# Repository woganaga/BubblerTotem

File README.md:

# BubblerTotem

Bubble-LED-Rage-Totem: a battery-powered LED totem / bubble machine — 6
stacked rings of 27 WS2811 LEDs (162 total, an unrolled 27×6 cylinder) plus a
bubble motor, driven by an ESP32-S3 with an INMP441 I2S microphone for
sound-reactive effects.

The firmware is a customized fork of
[WLED-MM (MoonModules)](https://github.com/MoonModules/WLED-MM), chosen for
its advanced audio visualizations.

## Project layout

| Path | Status | What it is |
|---|---|---|
| [`WLED-MM/`](WLED-MM/) | **active** | Firmware: WLED-MM fork (git submodule, branch `bubbler`). Totem customizations live in its `bubbler/` folder + usermods. |
| [`BubblerAnalyzer/`](BubblerAnalyzer/) | active | Offline audio/beat-detection analysis: pulls synchronized mic WAV + DSP metadata captures from the device over WiFi and diffs the pipeline against an offline replica. |
| [`docs/`](docs/) | active (port pending) | Web Bluetooth control app (GitHub Pages). Built for the v1 firmware; will be reworked once WLED-MM gets its BLE usermod. |
| [`archive/Bubbler-pio/`](archive/Bubbler-pio/) | retired | v1 custom firmware (PlatformIO): effects engine, palettes/presets, BLE protocol, beat detection. Superseded by the WLED-MM fork; kept as reference — the beat-detection work (comb tempo picker) and BLE chunk protocol are worth porting. |
| [`archive/BubblerIno/`](archive/BubblerIno/) | retired | Original Arduino IDE sketch (v0). |

## Working with the firmware submodule

```sh
git clone --recurse-submodules https://github.com/woganaga/BubblerTotem.git
cd BubblerTotem/WLED-MM
# copy bubbler/platformio_bubbler.sample.ini -> platformio_override.ini, add WiFi creds
pio run -e bubbler_totem
```

The submodule's `origin` is the `woganaga/WLED-MM` fork; `upstream` is
MoonModules. Custom work stays on the `bubbler` branch in low-collision
surfaces (`bubbler/`, usermods, the gitignored `platformio_override.ini`) so
upstream merges stay painless.

## Hardware map

| Function | GPIO |
|---|---|
| LED chain A (rings 3,2,1 — 81 px, WS2811 GRB) | 4 |
| LED chain B (rings 4,5,6 — 81 px) | 5 |
| INMP441 mic SCK / WS / SD | 44 / 7 / 8 |
| Bubble motor (planned) | 15 |
| RS485 command receiver (planned) | 1, 2, 42 |
| Onboard status LED (active low) | 21 |

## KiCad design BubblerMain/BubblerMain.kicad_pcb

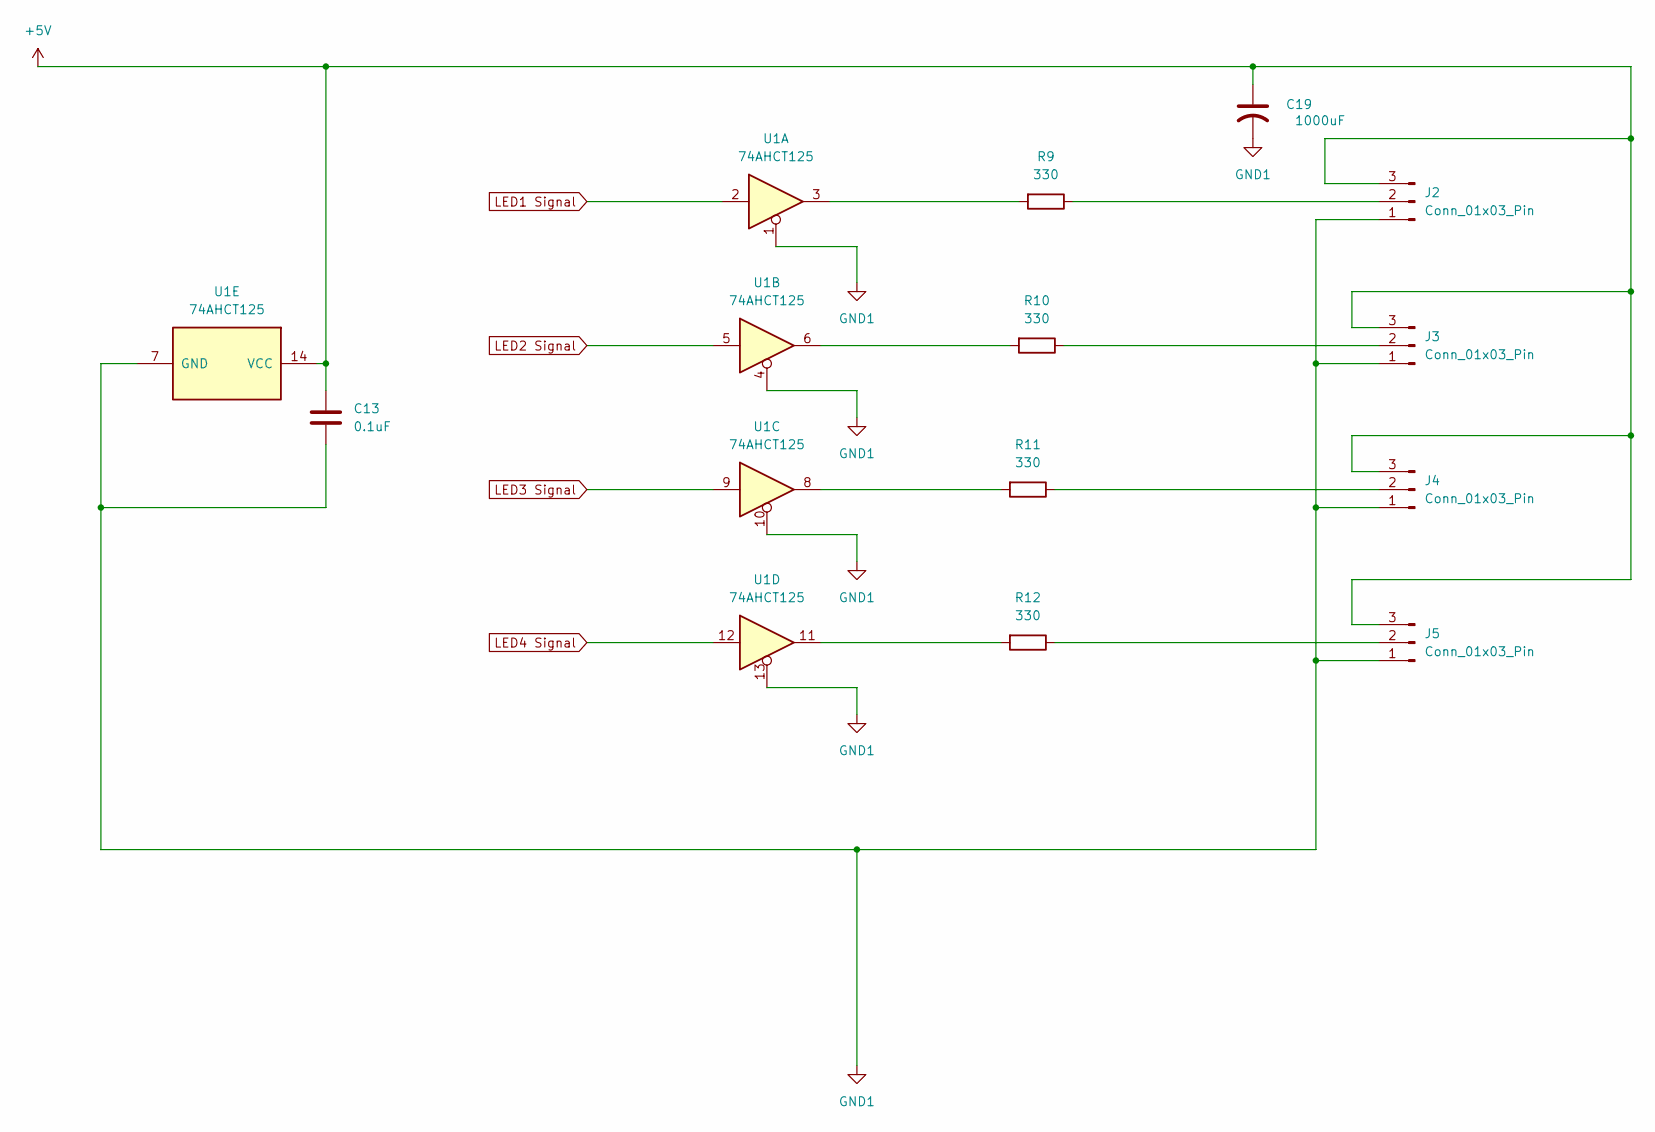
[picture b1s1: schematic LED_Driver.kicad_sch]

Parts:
C13: 0.1uF; C_1206_3216Metric_Pad1.33x1.80mm_HandSolder
C19: 1000uF; CP_Elec_10x10
J2, J3, J4, J5: Conn_01x03_Pin; JST_XH_B3B-XH-AM_1x03_P2.50mm_Vertical
R9, R10, R11, R12: 330; R_1206_3216Metric_Pad1.30x1.75mm_HandSolder
U1: 74AHCT125; SOIC-14_3.9x8.7mm_P1.27mm; LCSC C2675672

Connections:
+5V: C13.1, C19.1, J2.3, J3.3, J4.3, J5.3, U1.14 (VCC); also elsewhere on the board
GND1: C13.2, C19.2, J2.1, J3.1, J4.1, J5.1, U1.1, U1.4, U1.7 (GND), U1.10, U1.13; also elsewhere on the board
LED1 Signal: U1.2; also elsewhere on the board
LED2 Signal: U1.5; also elsewhere on the board
LED3 Signal: U1.9; also elsewhere on the board
LED4 Signal: U1.12; also elsewhere on the board
unnamed: J2.2, R9.1
unnamed: J3.2, R10.1
unnamed: J4.2, R11.1
unnamed: J5.2, R12.1
unnamed: R9.2, U1.3
unnamed: R10.2, U1.6
unnamed: R11.2, U1.8
unnamed: R12.2, U1.11

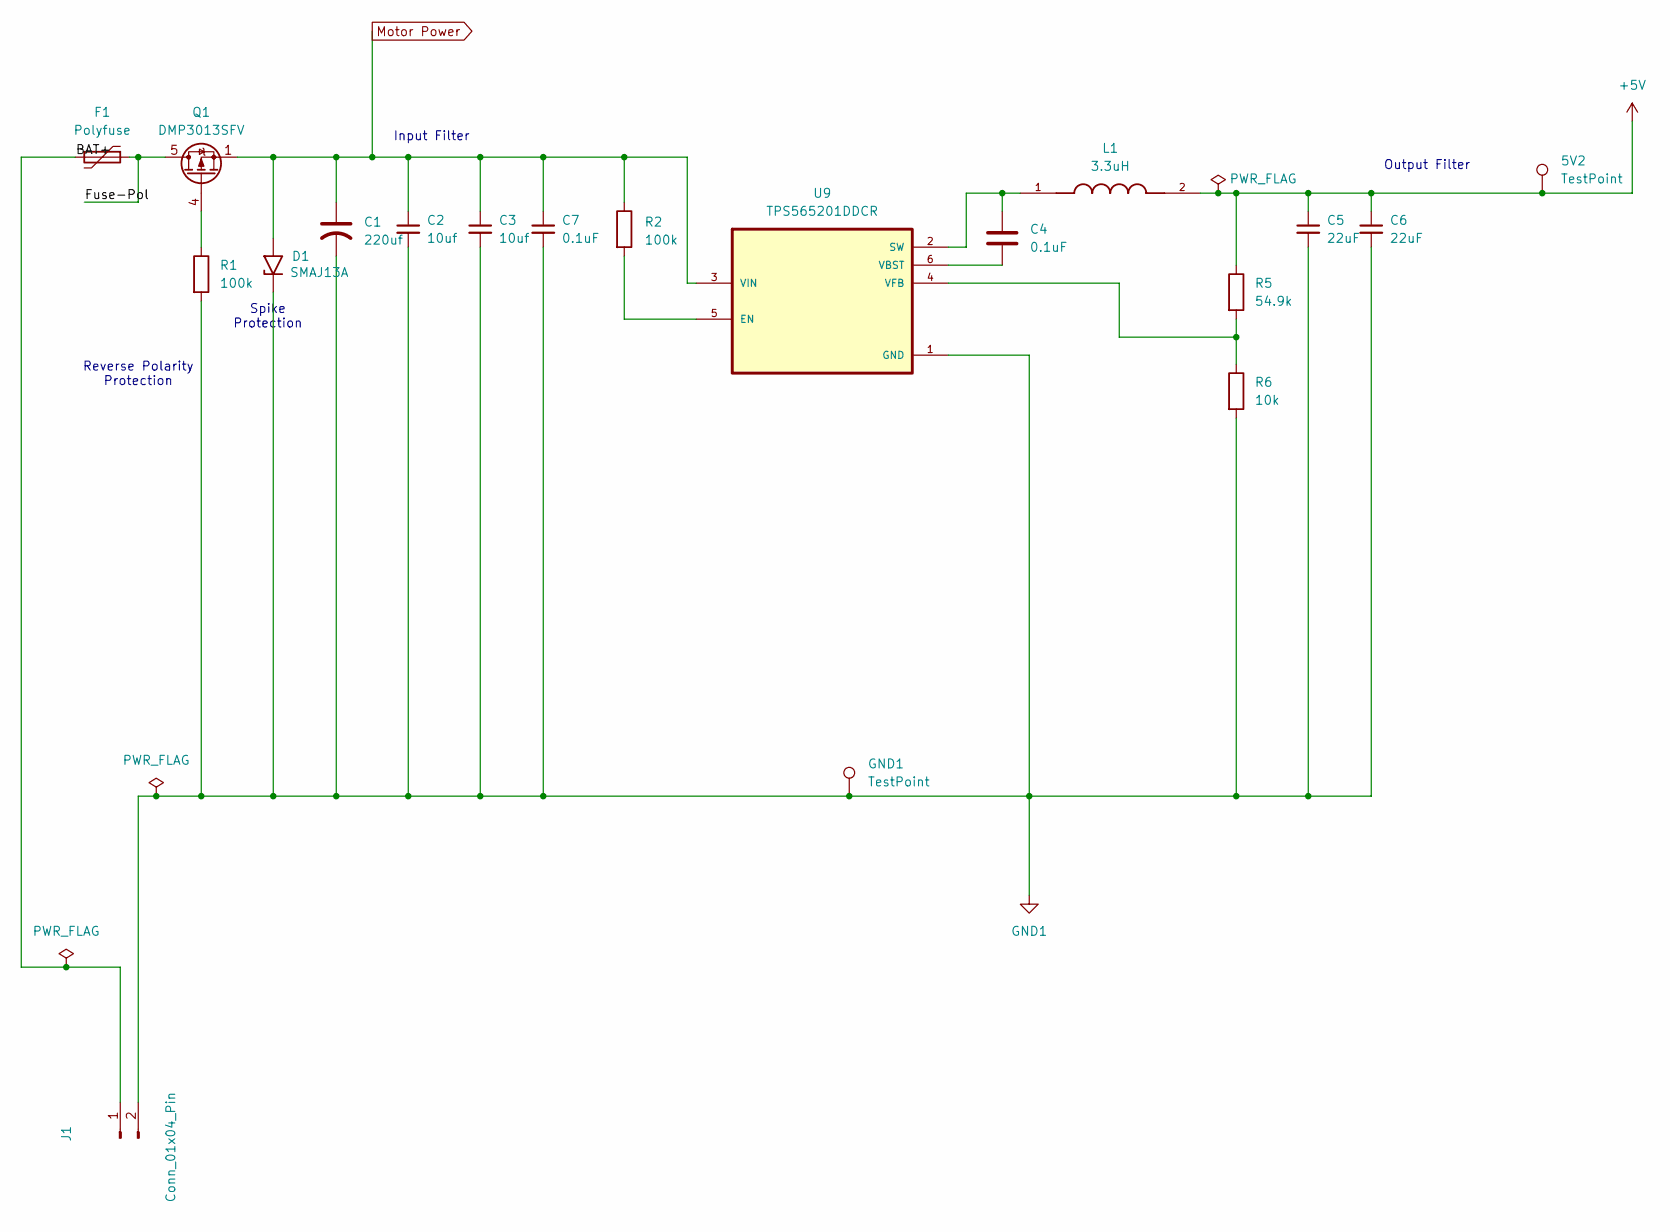
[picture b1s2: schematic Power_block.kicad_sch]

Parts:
5V2: TestPoint; TestPoint_Pad_2.0x2.0mm
C1: 220uf; CP_Elec_10x10
C2, C3: 10uf; C_1206_3216Metric_Pad1.33x1.80mm_HandSolder
C4: 0.1uF; C_1210_3225Metric_Pad1.33x2.70mm_HandSolder
C5, C6: 22uF; C_1210_3225Metric_Pad1.33x2.70mm_HandSolder
C7: 0.1uF; C_1206_3216Metric_Pad1.33x1.80mm_HandSolder
D1: SMAJ13A; D_SMA
F1: Polyfuse; Fuse_1812_4532Metric
GND1: TestPoint; TestPoint_Pad_2.0x2.0mm
J1: Conn_01x04_Pin; JST_XH_B2B-XH-AM_1x02_P2.50mm_Vertical
L1: 3.3uH; IND_SPM6530T-3R3M; PARTREV N/A; LCSC C76856
Q1: DMP3013SFV; Diodes_PowerDI3333-8; LCSC C264098
R1, R2: 100k; R_1206_3216Metric_Pad1.30x1.75mm_HandSolder
R5: 54.9k; R_1206_3216Metric_Pad1.30x1.75mm_HandSolder
R6: 10k; R_1206_3216Metric_Pad1.30x1.75mm_HandSolder
U9: TPS565201DDCR; SOT95P280X110-6N; LCSC C327676

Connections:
+5V: 5V2.1, C5.1, C6.1, L1.2, R5.1; also elsewhere on the board
/Power Block/BAT+: F1.2, J1.1
/Power Block/Fuse-Pol: F1.1, Q1.5 (D)
GND1: C1.2, C2.2, C3.2, C5.2, C6.2, C7.2, D1.1 (A1), GND1.1, J1.2, R1.2, R6.2, U9.1 (GND); also elsewhere on the board
Motor Power: C1.1, C2.1, C3.1, C7.1, D1.2 (A2), Q1.1 (S), Q1.2 (S), Q1.3 (S), R2.1, U9.3 (VIN); also elsewhere on the board
unnamed: Q1.4 (G), R1.1
unnamed: R2.2, U9.5 (EN)
unnamed: C4.1, L1.1, U9.2 (SW)
unnamed: C4.2, U9.6 (VBST)
unnamed: R5.2, R6.1, U9.4 (VFB)

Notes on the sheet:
Output Filter
Input Filter
Spike Protection
Reverse Polarity Protection

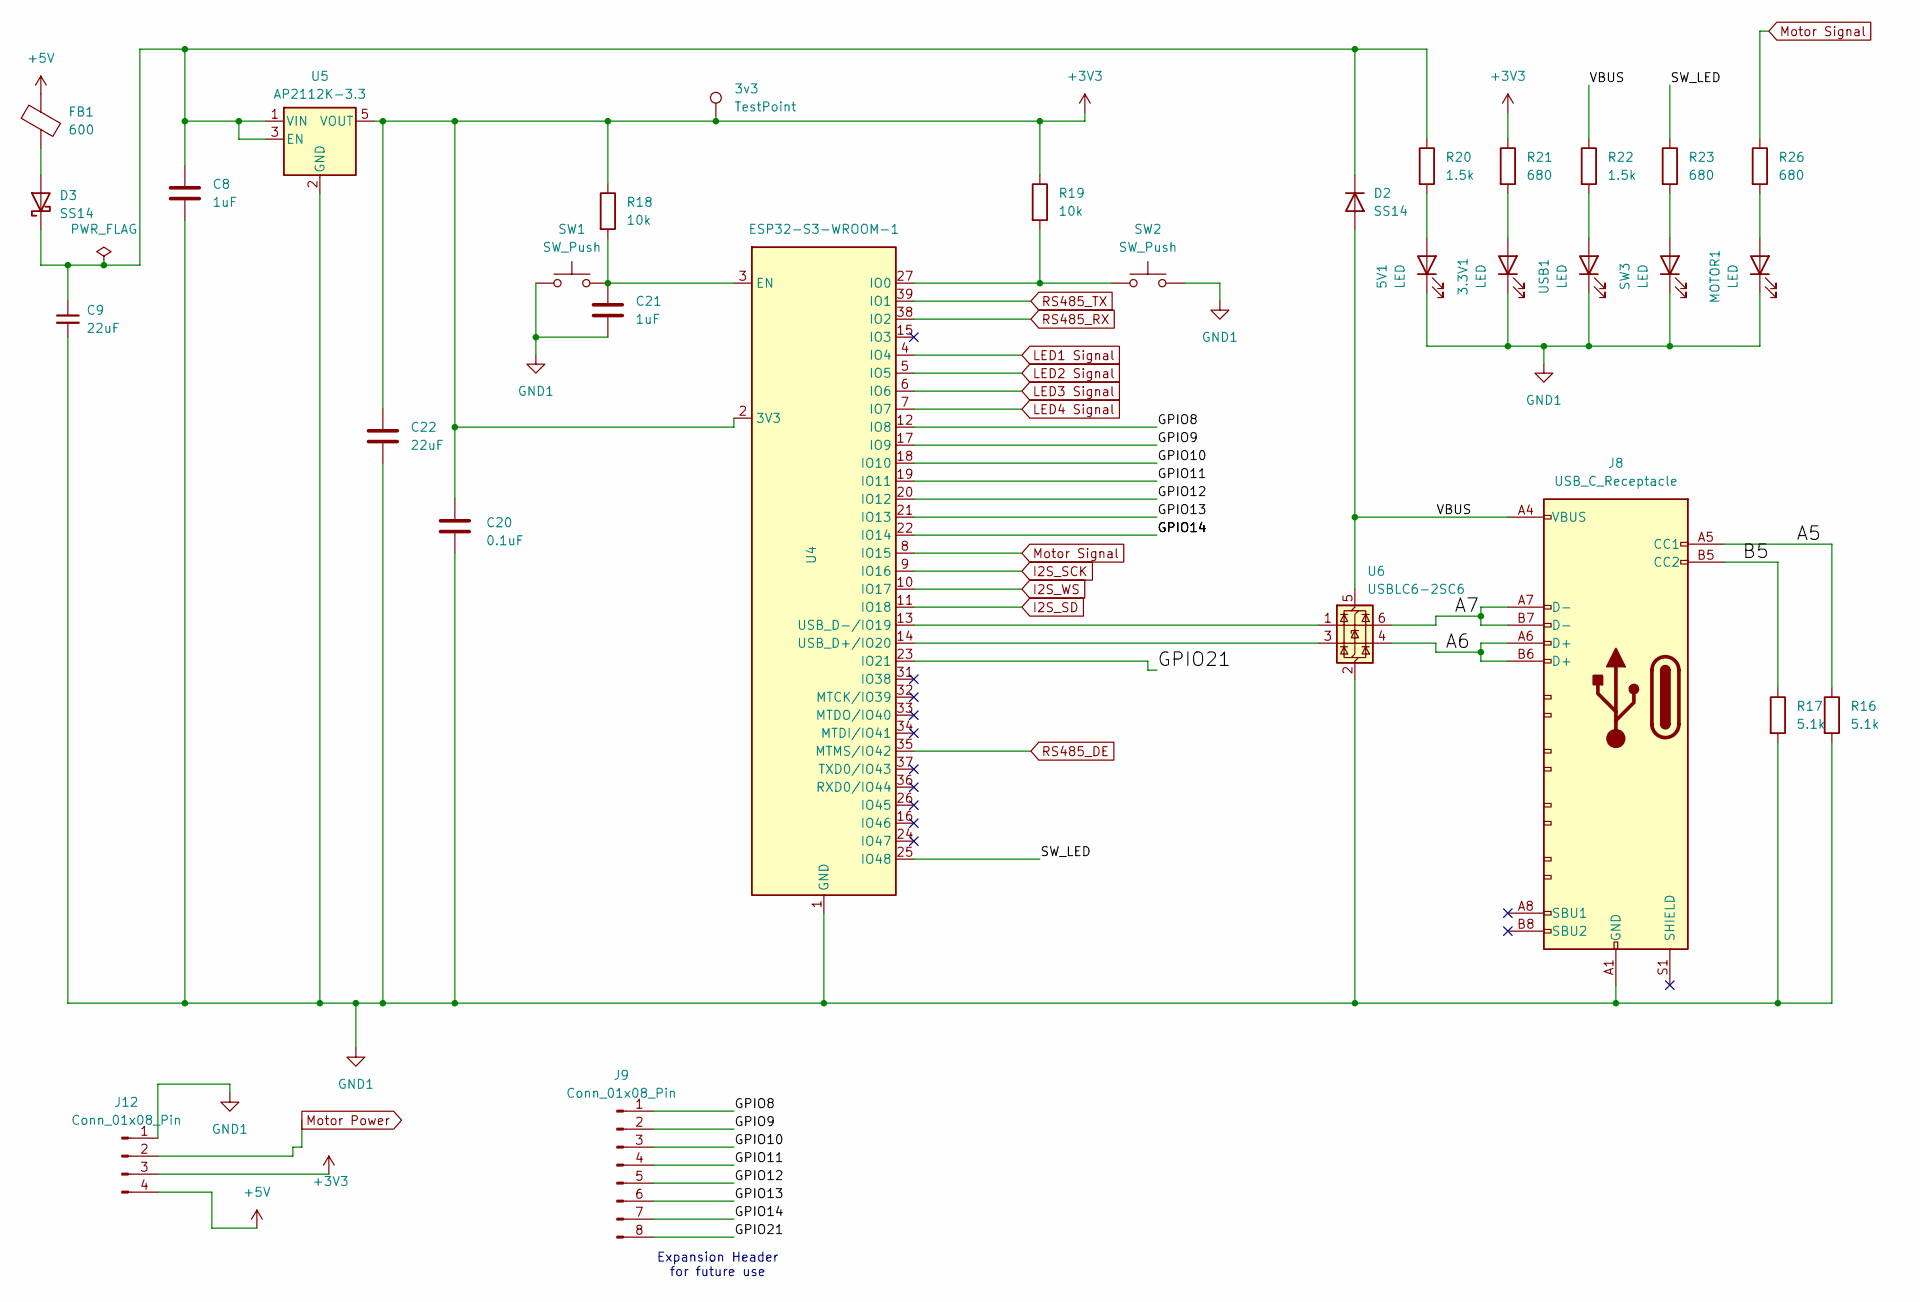
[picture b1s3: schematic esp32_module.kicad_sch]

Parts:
3.3V1, 5V1: LED; LED_1206_3216Metric_Pad1.42x1.75mm_HandSolder
3v3: TestPoint; TestPoint_Pad_2.0x2.0mm
C8, C21: 1uF; C_1206_3216Metric_Pad1.33x1.80mm_HandSolder
C9, C22: 22uF; C_1210_3225Metric_Pad1.33x2.70mm_HandSolder
C20: 0.1uF; C_1206_3216Metric_Pad1.33x1.80mm_HandSolder
D2, D3: SS14; D_SMA
FB1: 600; L_1206_3216Metric
J8: USB_C_Receptacle; USB_C_Receptacle_HCTL_HC-TYPE-C-16P-01A
J9: Conn_01x08_Pin; PinHeader_1x08_P2.54mm_Vertical
J12: Conn_01x08_Pin; PinHeader_1x04_P2.54mm_Vertical
MOTOR1: LED; LED_1206_3216Metric_Pad1.42x1.75mm_HandSolder
R16, R17: 5.1k; R_1206_3216Metric_Pad1.30x1.75mm_HandSolder
R18, R19: 10k; R_1206_3216Metric_Pad1.30x1.75mm_HandSolder
R20, R22: 1.5k; R_1206_3216Metric_Pad1.30x1.75mm_HandSolder
R21, R23, R26: 680; R_1206_3216Metric_Pad1.30x1.75mm_HandSolder
SW1, SW2: SW_Push; SW_SPST_PTS645Sx43SMTR92
SW3: LED; LED_1206_3216Metric_Pad1.42x1.75mm_HandSolder
U4: ESP32-S3-WROOM-1; ESP32-S3-WROOM-2; LCSC C2913198
U5: AP2112K-3.3; SOT-23-5; LCSC C23380830
U6: USBLC6-2SC6; SOT-23-6; LCSC C2827654
USB1: LED; LED_1206_3216Metric_Pad1.42x1.75mm_HandSolder

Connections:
+3V3: 3v3.1, C20.1, C22.1, J12.3, R18.1, R19.1, R21.1, U4.2 (3V3), U5.5 (VOUT); also elsewhere on the board
+5V: FB1.1, J12.4; also elsewhere on the board
/ESP32/A6: J8.A6 (D+), J8.B6 (D+), U6.4 (I/O2)
/ESP32/A7: J8.A7 (D-), J8.B7 (D-), U6.6 (I/O1)
/ESP32/GPIO8: J9.1, U4.12 (IO8)
/ESP32/GPIO9: J9.2, U4.17 (IO9)
/ESP32/GPIO10: J9.3, U4.18 (IO10)
/ESP32/GPIO11: J9.4, U4.19 (IO11)
/ESP32/GPIO12: J9.5, U4.20 (IO12)
/ESP32/GPIO13: J9.6, U4.21 (IO13)
/ESP32/GPIO14: J9.7, U4.22 (IO14)
/ESP32/GPIO21: J9.8, U4.23 (IO21)
/ESP32/SW_LED: R23.1, U4.25 (IO48)
/ESP32/VBUS: D2.2 (A), J8.A4 (VBUS), J8.A9 (VBUS), J8.B4 (VBUS), J8.B9 (VBUS), R22.1, U6.5 (VBUS)
GND1: 3.3V1.1 (K), 5V1.1 (K), C8.2, C9.2, C20.2, C21.2, C22.2, J8.A1 (GND), J8.A12 (GND), J8.B1 (GND), J8.B12 (GND), J12.1, MOTOR1.1 (K), R16.2, R17.2, SW1.1, SW2.2, SW3.1 (K), U4.1 (GND), U4.40 (GND), U4.41 (GND), U5.2 (GND), U6.2 (GND), USB1.1 (K); also elsewhere on the board
I2S_SCK: U4.9 (IO16); also elsewhere on the board
I2S_SD: U4.11 (IO18); also elsewhere on the board
I2S_WS: U4.10 (IO17); also elsewhere on the board
LED1 Signal: U4.4 (IO4); also elsewhere on the board
LED2 Signal: U4.5 (IO5); also elsewhere on the board
LED3 Signal: U4.6 (IO6); also elsewhere on the board
LED4 Signal: U4.7 (IO7); also elsewhere on the board
Motor Power: J12.2; also elsewhere on the board
Motor Signal: R26.1, U4.8 (IO15); also elsewhere on the board
unnamed 26: 3.3V1.2 (A), R21.2; also elsewhere on the board
unnamed 27: 5V1.2 (A), R20.2; also elsewhere on the board
unnamed: C8.1, C9.1, D2.1 (K), D3.1 (K), R20.1, U5.1 (VIN), U5.3 (EN)
unnamed: D3.2 (A), FB1.2
unnamed: MOTOR1.2 (A), R26.2
unnamed 45: R23.2, SW3.2 (A); also elsewhere on the board
unnamed: C21.1, R18.2, SW1.2, U4.3 (EN)
unnamed: R19.2, SW2.1, U4.27 (IO0)
unnamed: U4.14 (USB_D+/IO20), U6.3 (I/O2)
unnamed: U4.13 (USB_D-/IO19), U6.1 (I/O1)
unnamed 57: R22.2, USB1.2 (A); also elsewhere on the board
RS485_DE: U4.35 (MTMS/IO42); also elsewhere on the board
RS485_RX: U4.38 (IO2); also elsewhere on the board
RS485_TX: U4.39 (IO1); also elsewhere on the board

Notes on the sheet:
Expansion Header for future use

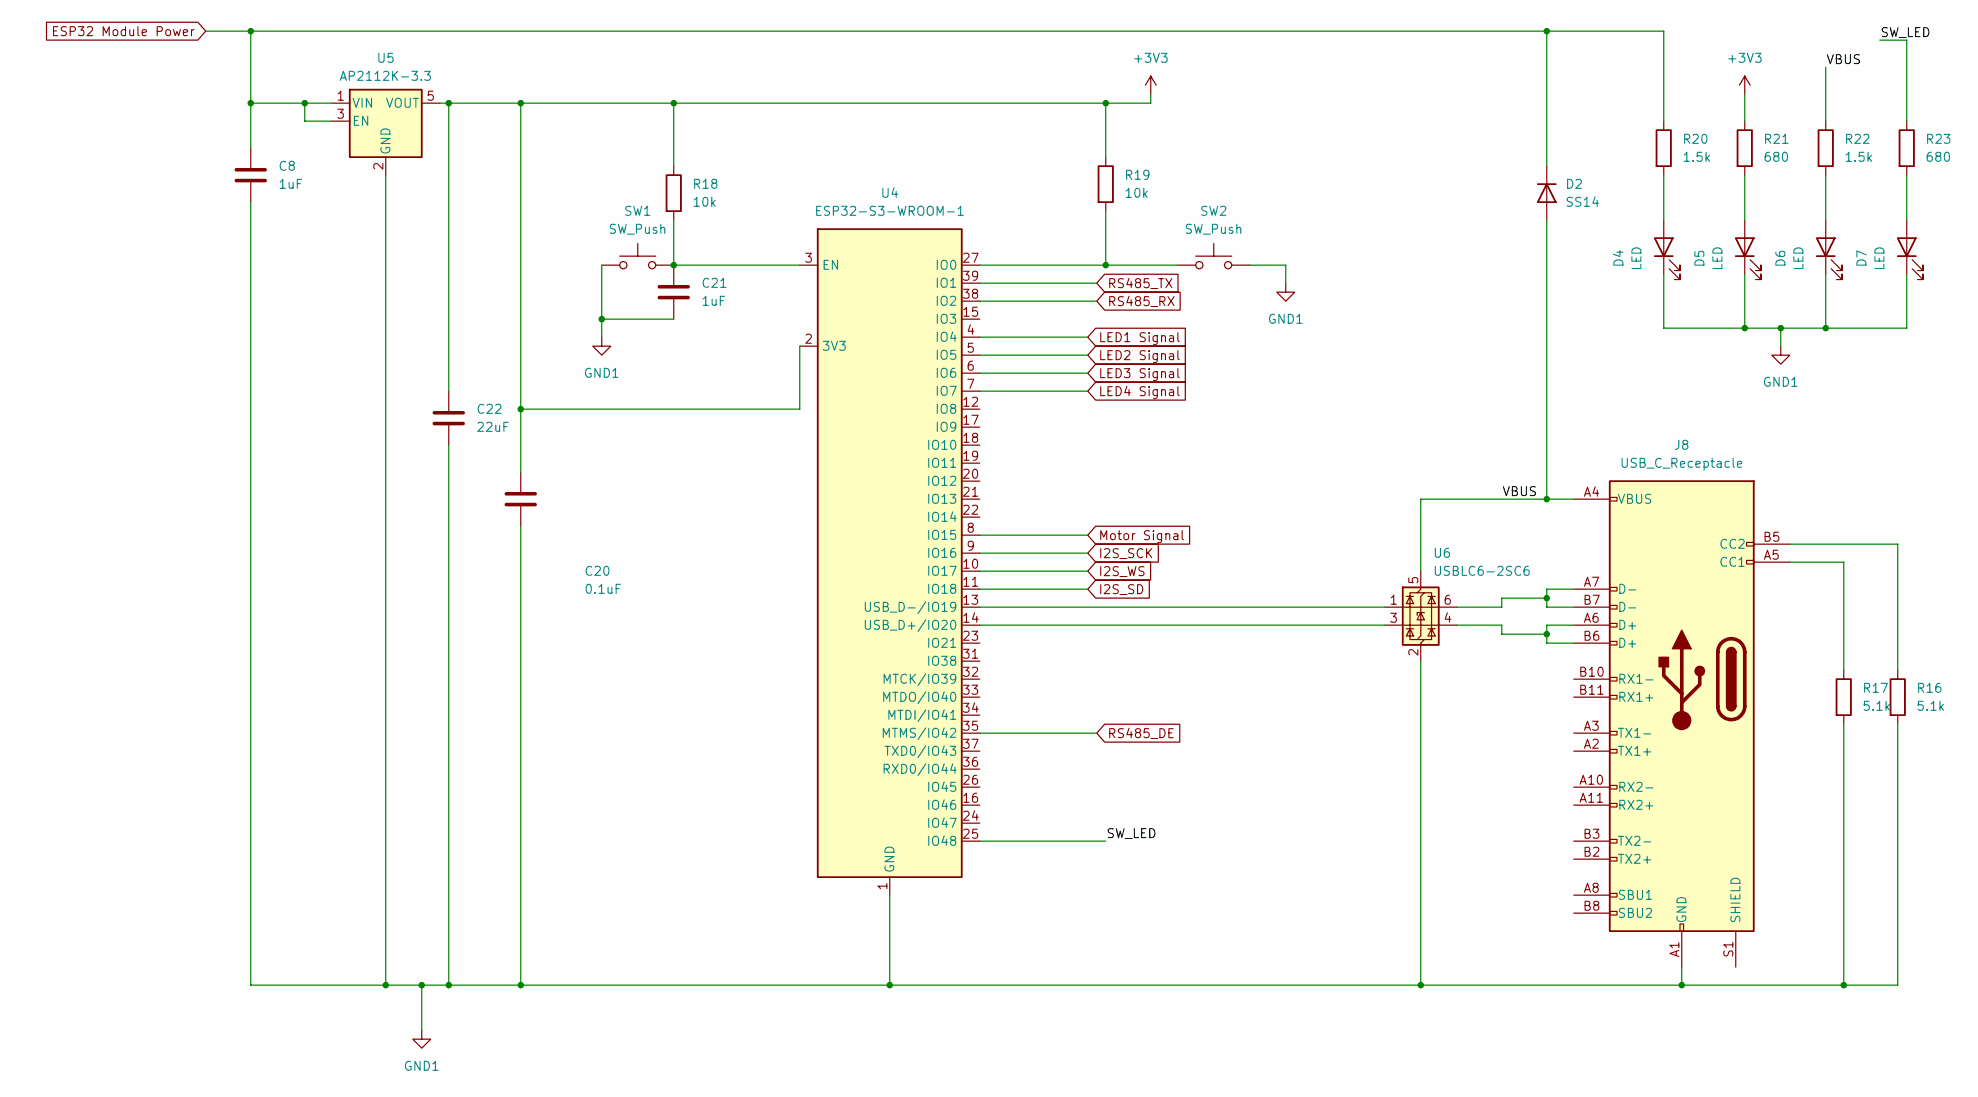
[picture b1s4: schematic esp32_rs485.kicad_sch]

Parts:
C8, C21: 1uF
C20: 0.1uF
C22: 22uF
D2: SS14
D4, D5, D6, D7: LED
J8: USB_C_Receptacle
R16, R17: 5.1k
R18, R19: 10k
R20, R22: 1.5k
R21, R23: 680
SW1, SW2: SW_Push
U4: ESP32-S3-WROOM-1; ESP32-S3-WROOM-2
U5: AP2112K-3.3; SOT-23-5
U6: USBLC6-2SC6; SOT-23-6

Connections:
+3V3: C20.1, C22.1, R18.1, R19.1, R21.1, U4.2 (3V3), U5.5 (VOUT); also elsewhere on the board
/ESP32/A6: J8.A6 (D+), J8.B6 (D+), U6.4 (I/O2)
/ESP32/A7: J8.A7 (D-), J8.B7 (D-), U6.6 (I/O1)
/ESP32/GPIO8: U4.12 (IO8); also elsewhere on the board
/ESP32/GPIO9: U4.17 (IO9); also elsewhere on the board
/ESP32/GPIO10: U4.18 (IO10); also elsewhere on the board
/ESP32/GPIO11: U4.19 (IO11); also elsewhere on the board
/ESP32/GPIO12: U4.20 (IO12); also elsewhere on the board
/ESP32/GPIO13: U4.21 (IO13); also elsewhere on the board
/ESP32/GPIO14: U4.22 (IO14); also elsewhere on the board
/ESP32/GPIO21: U4.23 (IO21); also elsewhere on the board
/ESP32/SW_LED: R23.1, U4.25 (IO48)
/ESP32/VBUS: D2.2 (A), J8.A4 (VBUS), J8.A9 (VBUS), J8.B4 (VBUS), J8.B9 (VBUS), R22.1, U6.5 (VBUS)
GND1: C8.2, C20.2, C21.2, C22.2, D4.1 (K), D5.1 (K), D6.1 (K), D7.1 (K), J8.A1 (GND), J8.A12 (GND), J8.B1 (GND), J8.B12 (GND), R16.2, R17.2, SW1.1, SW2.2, U4.1 (GND), U4.40 (GND), U4.41 (GND), U5.2 (GND), U6.2 (GND); also elsewhere on the board
I2S_SCK: U4.9 (IO16); also elsewhere on the board
I2S_SD: U4.11 (IO18); also elsewhere on the board
I2S_WS: U4.10 (IO17); also elsewhere on the board
LED1 Signal: U4.4 (IO4); also elsewhere on the board
LED2 Signal: U4.5 (IO5); also elsewhere on the board
LED3 Signal: U4.6 (IO6); also elsewhere on the board
LED4 Signal: U4.7 (IO7); also elsewhere on the board
Motor Signal: U4.8 (IO15); also elsewhere on the board
unnamed 26: D5.2 (A), R21.2; also elsewhere on the board
unnamed 27: D4.2 (A), R20.2; also elsewhere on the board
unnamed 28: C8.1, D2.1 (K), R20.1, U5.1 (VIN), U5.3 (EN); also elsewhere on the board
unnamed 45: D7.2 (A), R23.2; also elsewhere on the board
unnamed: C21.1, R18.2, SW1.2, U4.3 (EN)
unnamed: R19.2, SW2.1, U4.27 (IO0)
unnamed: U4.14 (USB_D+/IO20), U6.3 (I/O2)
unnamed: U4.13 (USB_D-/IO19), U6.1 (I/O1)
unnamed 57: D6.2 (A), R22.2; also elsewhere on the board
RS485_DE: U4.35 (MTMS/IO42); also elsewhere on the board
RS485_RX: U4.38 (IO2); also elsewhere on the board
RS485_TX: U4.39 (IO1); also elsewhere on the board

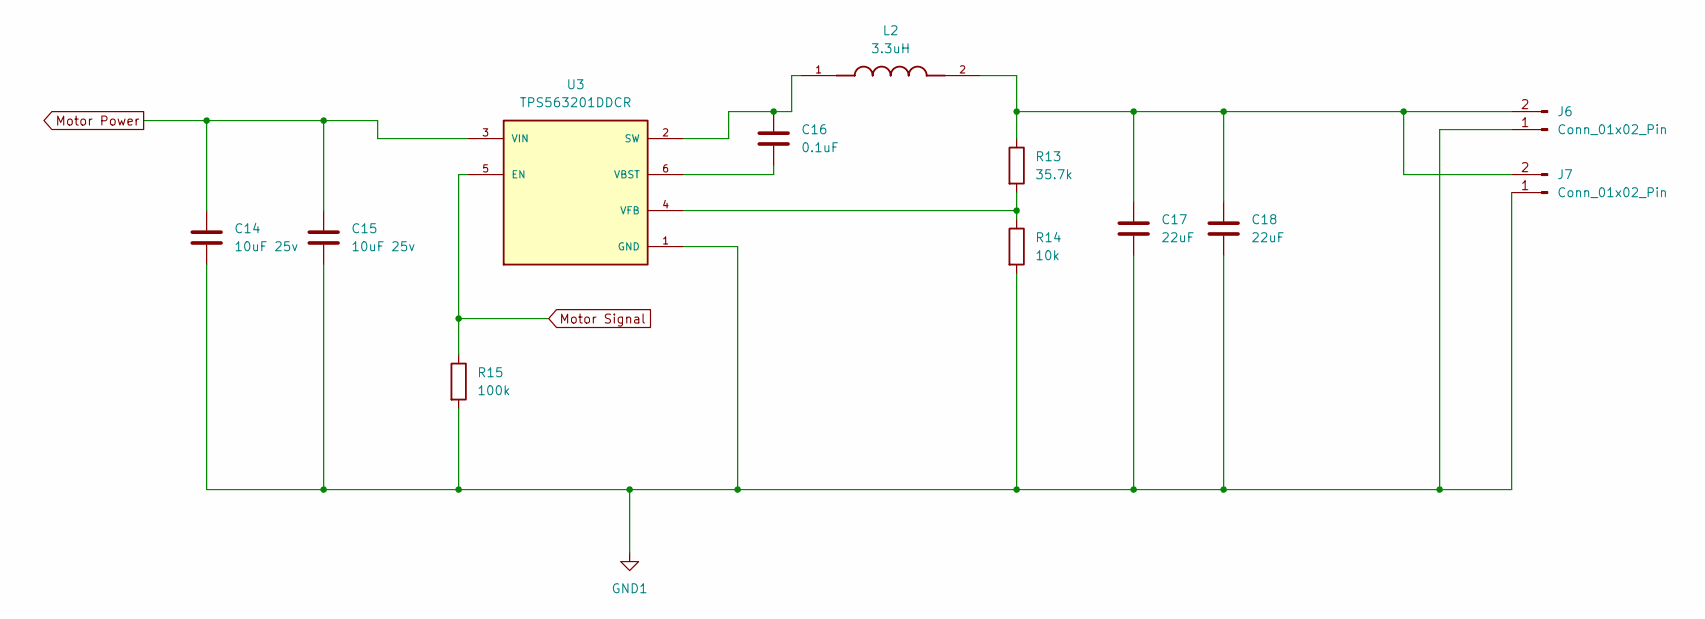
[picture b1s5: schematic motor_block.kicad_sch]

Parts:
C14, C15: 10uF 25v; C_1206_3216Metric_Pad1.33x1.80mm_HandSolder
C16: 0.1uF; C_1206_3216Metric_Pad1.33x1.80mm_HandSolder
C17, C18: 22uF; C_1210_3225Metric_Pad1.33x2.70mm_HandSolder
J6, J7: Conn_01x02_Pin; JST_XH_B2B-XH-AM_1x02_P2.50mm_Vertical
L2: 3.3uH; IND_SPM6530T-3R3M; PARTREV N/A; LCSC C76856
R13: 35.7k; R_1206_3216Metric_Pad1.30x1.75mm_HandSolder
R14: 10k; R_1206_3216Metric_Pad1.30x1.75mm_HandSolder
R15: 100k; R_1206_3216Metric_Pad1.30x1.75mm_HandSolder
U3: TPS563201DDCR; TSOT-23-6_HandSoldering; PARTREV December 2015; LCSC C116592

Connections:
GND1: C14.2, C15.2, C17.2, C18.2, J6.1, J7.1, R14.2, R15.2, U3.1 (GND); also elsewhere on the board
Motor Power: C14.1, C15.1, U3.3 (VIN); also elsewhere on the board
Motor Signal: R15.1, U3.5 (EN); also elsewhere on the board
unnamed: C17.1, C18.1, J6.2, J7.2, L2.2, R13.1
unnamed: C16.1, L2.1, U3.2 (SW)
unnamed: C16.2, U3.6 (VBST)
unnamed: R13.2, R14.1, U3.4 (VFB)

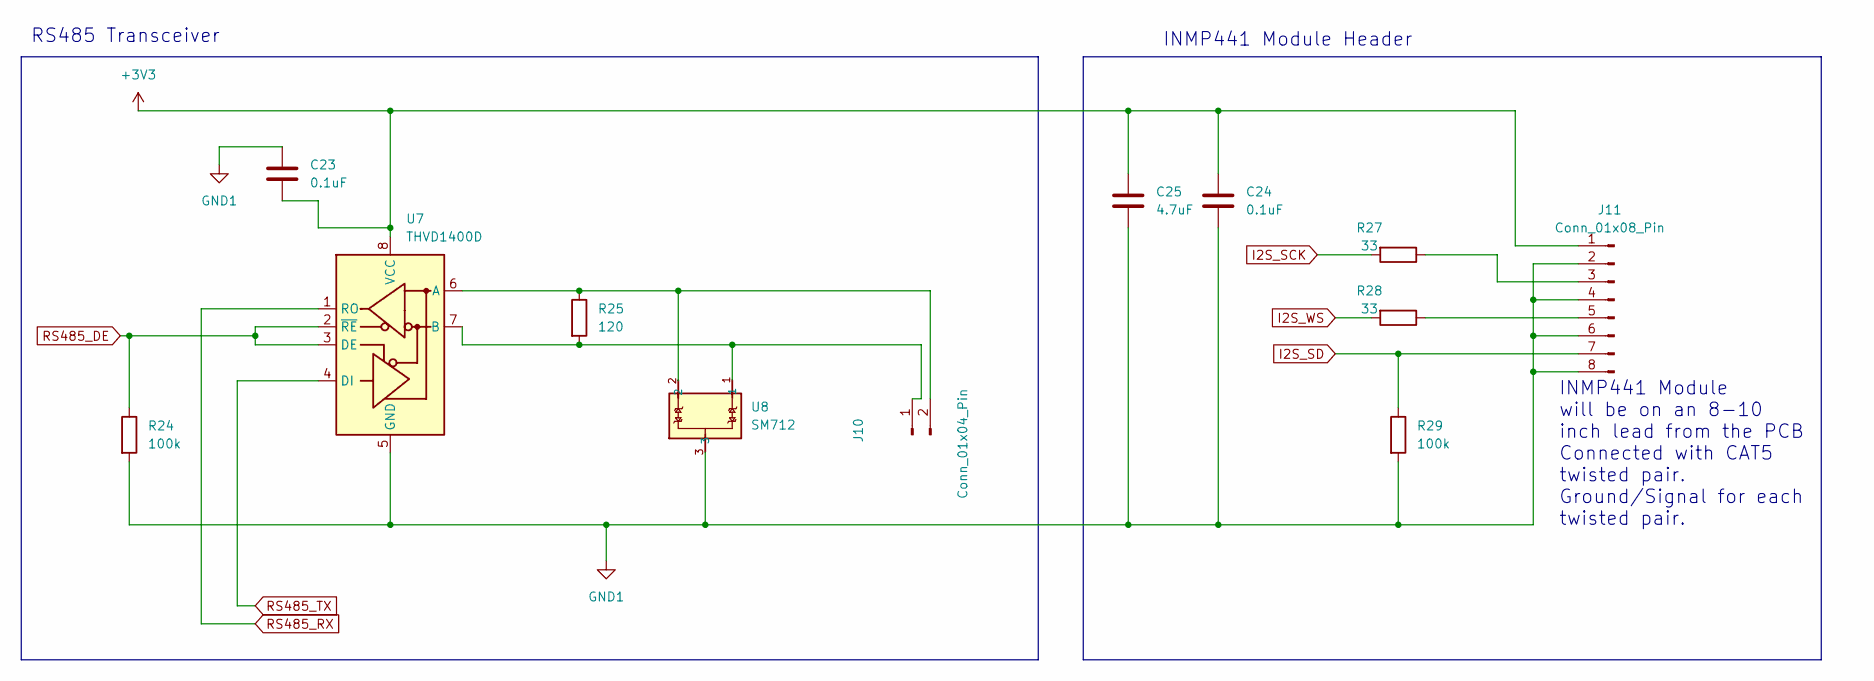
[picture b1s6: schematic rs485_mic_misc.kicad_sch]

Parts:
C23, C24: 0.1uF; C_1206_3216Metric_Pad1.33x1.80mm_HandSolder
C25: 4.7uF; C_1206_3216Metric_Pad1.33x1.80mm_HandSolder
J10: Conn_01x04_Pin; JST_XH_B2B-XH-AM_1x02_P2.50mm_Vertical
J11: Conn_01x08_Pin; JST_XH_B8B-XH-AM_1x08_P2.50mm_Vertical
R24, R29: 100k; R_1206_3216Metric_Pad1.30x1.75mm_HandSolder
R25: 120; R_1206_3216Metric_Pad1.30x1.75mm_HandSolder
R27, R28: 33; R_1206_3216Metric_Pad1.30x1.75mm_HandSolder
U7: THVD1400D; SOIC-8_3.9x4.9mm_P1.27mm; LCSC C3235232
U8: SM712; SOT23-WIDE; LCSC C502564

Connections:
+3V3: C23.1, C24.1, C25.1, J11.1, U7.8 (VCC); also elsewhere on the board
GND1: C23.2, C24.2, C25.2, J11.2, J11.4, J11.6, J11.8, R24.2, R29.2, U7.5 (GND), U8.3; also elsewhere on the board
I2S_SCK: R27.2; also elsewhere on the board
I2S_SD: J11.7, R29.1; also elsewhere on the board
I2S_WS: R28.2; also elsewhere on the board
unnamed: J10.1, R25.2, U7.7 (B), U8.1
unnamed: J10.2, R25.1, U7.6 (A), U8.2
unnamed: J11.3, R27.1
unnamed: J11.5, R28.1
RS485_DE: R24.1, U7.2 (~RE), U7.3 (DE); also elsewhere on the board
RS485_RX: U7.1 (RO); also elsewhere on the board
RS485_TX: U7.4 (DI); also elsewhere on the board

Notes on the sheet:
RS485 Transceiver
INMP441 Module Header
INMP441 Module will be on an 8-10 inch lead from the PCB Connected with CAT5 twisted pair. Ground/Signal for each twisted pair.

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
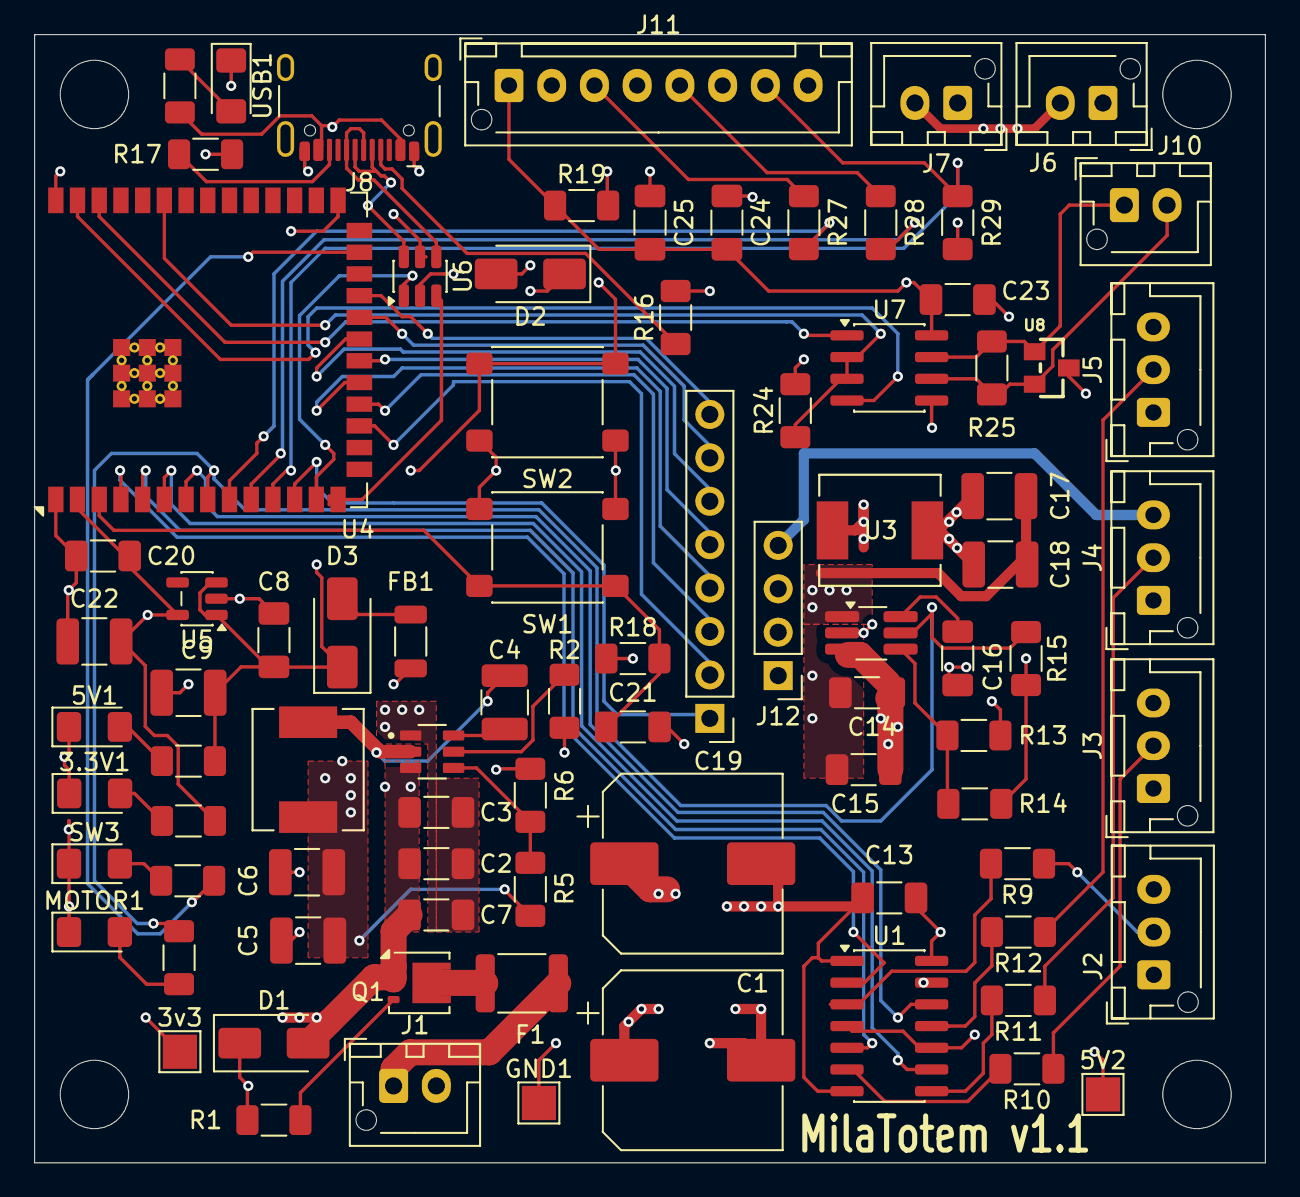
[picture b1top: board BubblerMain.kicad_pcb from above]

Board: 4 copper layers, 72.0 x 66.0 mm, 85 parts (0 on the bottom side), 63 nets.
